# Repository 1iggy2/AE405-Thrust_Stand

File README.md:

# AE405 Thrust Stand

Aero 405 Thrust Stand Project

*By Cameron Gable (1iggy2), Anthony Russo, Hogan Hsu, Sergio Ramirez Sabogal, Brian Sandor*

This project is aimed towards providing a thrust testing stand for brushless electric motors
and propellers used by student project teams as part of Professor George Halow’s AERO 495
course. Prof. Halow has indicated that there is currently a need for some of the project teams that
are part of his course to have an easy way to test the thrust capabilities of their electric motors and
propellers for applications ranging from quadcopters to fixed wing aircraft. Our project concept is
therefore a proposal to design, build, and test a modular thrust test stand that allows for multiple
motor and propeller sizes to be tested safely and effectively by any of the teams participating in
AERO 495. This test stand will use sensors to measure thrust, torque, voltage, current, and RPM
and involve a processing system for automated data collection for simple export to software like
Excel or MatLab for analysis.

Table of Contents
=================

<!--ts-->
   * [Instruction Manual](#instruction-manual)
      * [Safety Considerations](#safety-considerations)
      * [How to Use the Remote](#how-to-use-the-remote)
      * [How to Use the Base Station](#how-to-use-the-base-station)
   * [Construction Guide](#construction-guide)
      * [Wiring](#wiring)
        * [Remote](#remote)
        * [Base Station](#base-station)
      * [Thrust Stand](#thrust-stand)
   * [Design Justification](#design-justification)
      * [Code](#code)
        * [Base Station Logic](base-station-logic)
        * [Remote GUI Explaination](remote-gui-explaination)
      * [Physical Structure Analysis and Testing](physical-structure-analysis-and-testing)
        * [Thrust Stand Simulation](thrust-stand-simulation)
<!--te-->

## Instruction Manual

### Safety Considerations

Be careful when near spinning and/or powered propellers they can and will maim you. Please remove all propellers while working on the thrust stand. Propellers of all sizes are dangerous and deserve your respect. Please use the remote to remain clear of the spinning blades of death, and ensure you have a way to break the physical circuit from a distance.

### How to Use the Remote

The remote connects to the base station using an nRF24L01 radio transciever. When powering on the remote from a computer or USB power supply you will be prompted to select a test to perform. The test selection buttons are on the left hand side of the remote and ordered as seen below:
* TS - Throttle Sweep
* CT - Constant Throttle
* ST - Stress Test

You then will use the ← (left), → (right), and ⌂ (select) buttons to enter your chosen testing parameters. These parameters are:
  
| Parameter |     Description    |  Throttle Sweep |    Constant Throttle    |     Stress Test     |
|:---------:|:------------------:|:---------------:|:-----------------------:|:-------------------:|
|     A     |      Test Type     |        1        |            2            |          3          |
|    BBB    |  Primary Throttle  | Bottom of Sweep | Constant Throttle Value | High Throttle Value |
|    CCC    | Secondary Throttle |   Top of Sweep  |           N/A           |  Low Throttle Value |
|    DDD    |      Test Time     | Total Test Time |     Total Test Time     |   Total Test Time   |
|    EEE    |      Step Time     |    Step Time    |           N/A           |    Switching Time   |

Before clicking to confirm your test selection and start your test you will be presented these values as a final check before sending the data to the base station. This will appear in the form:

* A:BBB:CCC:DDD:EEE

After the data is sent to the base station and the test begins simply click the ⌂ (select) button to send a cancel signal to the base station. In case of communication failure it is always important to have a safe method to physically break the circuit in the case of a catastrophic testing failure. 

### How to Use the Base Station

The base station is a rather hands off piece of equipment. You should not be interacting with it during testing, only monitoring. You may want to set your own safety parameters or recalibrate the test stand. In that case I recommend modifying the parameters in the base station file: [Mega_BaseStation.ino](https://github.com/1iggy2/AE405-Thrust_Stand/blob/main/Mega_BaseStation/Mega_BaseStation.ino) If you do this please submit your calibration to this Github page for posterity. To gather data you will need to insert a FAT32 or FAT16 formatted microSD card into the [Adafruit MicroSD card breakout board+](https://www.adafruit.com/product/254) for the data to be recorded. The data will be recorded to the microSD card in the format shown below. 

| AERO 405 Thrust Stand |                       Winter 2021                      |         |             | Cameron Gable |
|:---------------------:|:------------------------------------------------------:|:-------:|:-----------:|:-------------:|
| Find Documentation at:| [Github](https://github.com/1iggy2/AE405-Thrust_Stand) |         |             |               |
|                       |                                                        |         |             |               |
|  Ambient Conditions:  |                                                        |         |             |               |
|      Temperature:     |                          VALUE                         | Celsius |             |               |
|       Pressure:       |                          VALUE                         | Pascals |             |               |
|                       |                                                        |         |             |               |
|       Thrust(N)       |                          Volts                         |   Amps  | Torque(n-m) |      RPM      |
|         VALUE         |                          VALUE                         |  VALUE  |    VALUE    |     VALUE     |

At this time analysis software is not being developed. It is an important feature to this project, and the relevant issue can be found [here.](https://github.com/1iggy2/AE405-Thrust_Stand/issues/9)

## Construction Guide

### Wiring

#### Remote
The wiring diagram for the remote has been completed in EAGLE. Completed PCB design Gerber files can be found [here.](https://github.com/1iggy2/AE405-Thrust_Stand/tree/main/CAD/RemotePCB) The connections on the diagram below are accurate for anyone who prefers to manufacture it on perf board. (Assembling via a PCB is certainly easier though).

#### Base Station
The wiring diagram for the base station was also completed in EAGLE. However, a PCB has not yet been designed and remains an [issue](https://github.com/1iggy2/AE405-Thrust_Stand/issues/3) for future work.

Please note in the EAGLE image above the pin locations are not accurate on the Arduino Mega, instead the nets have been named [PIN-PURPOSE].

### Thrust Stand

Our thrust stand has been designed with modularity as the main objective. The interchangeable
vertical arm lengths allow for testing to occur for a variety of propeller and motor sizes. This also
allows for the thrust stand to operate in both large and small wind tunnels, making test scheduling more convenient for the users. Our motor mounting plates will allow for the mounting of
various motors with different bolt patterns. The various sizes of these plates will allow for testing
on small motors and large motors on the same stand. 

Long Arm Render             |  Short Arm Render
  :-------------------------:|:-------------------------:
  |  

Our unique flexure torque measurement
device, seen below, allows for torque data to be collected from all ranges of motor sizes that fit on the thrust
testing stand. This innovation increases the effectiveness and accuracy of the data from other more
traditional torque measurement solutions. These system design choices increase the effectiveness
of our thrust stand and allow it to meet a wide variety of team’s thrust testing needs.

Our design also features a pivot comprised of two pillow blocks to minimize any stiction, or static friction. A beautiful render of this pivot is shown below. A majority of the parts purchased for the structural construction came from McMaster Carr.

## Design Justification

### Code

#### Base Station Logic

The Base Station is the measurement and data acquistion hub of this project. Tests will be run based on the Menu ID sent from the remote. Raw sensor output, calibration, and settings will be accessed via a physical button press and the serial monitor. This is due to RAM limitations in the Arduino Nano powering the Remote. A full flowchart of the logic is provided below.

#### Remote GUI Explaination

After initial testing of the remote GUI intiailly proposed it was apparent that the Arduino Nano did not have enough RAM to display the fully fleshed out GUI. In order to combat this we have designed a low menu count GUI to optimize the remote. This menu uses a minimal amount of unique screens to lower the RAM usage. The image below is the design flowchart for the optimized remote.

### Physical Structure Analysis

#### Thrust Stand Simulation

In order to model the thrust stand system in FEA many of the complex structures
were simplified. This included the flexure assembly being modelled as a rectangular block and
the bearing pivot being modelled as a bearing fixture. The CAD model was done in Solidworks
and the FEA was done in the Solidworks built-in simulation tool. The load cell and the sides of the
pivot were modelled as roller/slider fixtures so that they would be constrained in the plane but
can move laterally. The built-in 6061 aluminum alloy material model was applied to the model
due to convenience, which has the same properties as the 6105-T5 alloy, just a lower yield strength.
The mesh was generated using Solidworks’ automated mesh tool, but mesh control was applied
in order to ensure that there were at least 3 elements across each dimension to accurately model
the problem. In the image below, a zoomed in display of the maximum stress point is shown along with
the mesh for the max loading condition of 20 lbf of thrust and 15 lbf-in of torque on the long
arm model. The maximum stress ended up being in the same region for all the simulations, right
where the 90◦ bracket met the horizontal arm.

Another accuracy concern is the drag produced by inlet air during wind tunnel testing, particularly
on the vertical arm of the test stand. The load cell measuring thrust will not be able to distinguish between this drag force and a thrust difference, thus reducing accuracy. To make sure that
our measurement is as accurate as possible during these testing circumstances, we surveyed various cross-sectional shapes of the vertical beam using CFD simulations. STAR-CCM+ CFD simulations were used to model the drag of the
stand. Because the only variable between these design is the vertical beam cross-section, simulations were performed using the 15 inch beam by itself, with semicircular fairings, and with one
semicircular fairing on the front face and an elliptical section on the rear face to give the overall cross-section an airfoil shape. Seen in the table below.

| No Fairing | Semi-Circular Fairing | Airfoil Fairing |
|------------|-----------------------|-----------------|
|       |                  |            |

The simulations were then run with the respective beam suspended,
centered in a simulated 2 foot X 2 foot wind tunnel using iterations with intake airspeed of 11, 22,
34, 45, 56, and 67 miles per hour. The results are shown in the table below.

Plotted into a graph:

With this information we are designing a 3D printed airfoil to slot into the 8020 aluminium extrusion. We will also be putting our structure, shrouded with an aerodynamic
fairing, into the wind tunnel and testing the amount of drag that the system generates with the
goal of minimizing this effect. This will be to validate our simulations. 

We chose to use a NACA 0015 airfoil fairing for the vertical arm of the stand.

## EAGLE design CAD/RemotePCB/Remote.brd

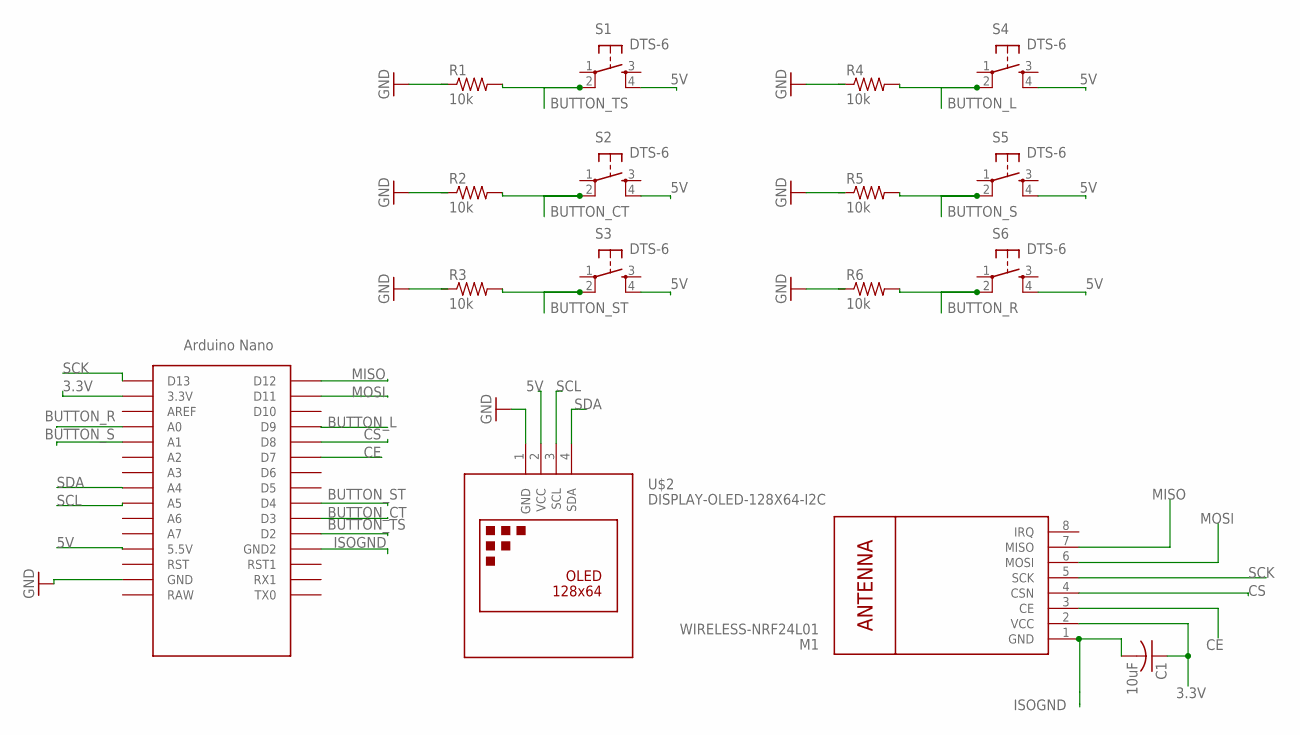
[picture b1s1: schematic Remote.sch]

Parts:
C1: 10uF; C025-030X050
M1: WIRELESS-NRF24L01
R1, R2, R3, R4, R5, R6: 10k; 0207/10
S1, S2, S3, S4, S5, S6: DTS-6
U$1: NANO
U$2: DISPLAY-OLED-128X64-I2C

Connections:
3.3V: C1.1, M1.2 (VCC), U$1.3.3V
5V: S1.4, S2.4, S3.4, S4.4, S5.4, S6.4, U$1.5V (5.5V), U$2.2 (VCC)
BUTTON_CT: R2.2, S2.2, U$1.D3
BUTTON_L: R4.2, S4.2, U$1.D9
BUTTON_R: R6.2, S6.2, U$1.A0
BUTTON_S: R5.2, S5.2, U$1.A1
BUTTON_ST: R3.2, S3.2, U$1.D4
BUTTON_TS: R1.2, S1.2, U$1.D2
CE: M1.3 (CE), U$1.D7
CS: M1.4 (CSN), U$1.D8
GND: R1.1, R2.1, R3.1, R4.1, R5.1, R6.1, U$1.GND, U$2.1 (GND)
ISOGND: C1.2, M1.1 (GND), U$1.GND1 (GND2)
MISO: M1.7 (MISO), U$1.D12
MOSI: M1.6 (MOSI), U$1.D11
SCK: M1.5 (SCK), U$1.D13
SCL: U$1.A5, U$2.3 (SCL)
SDA: U$1.A4, U$2.4 (SDA)

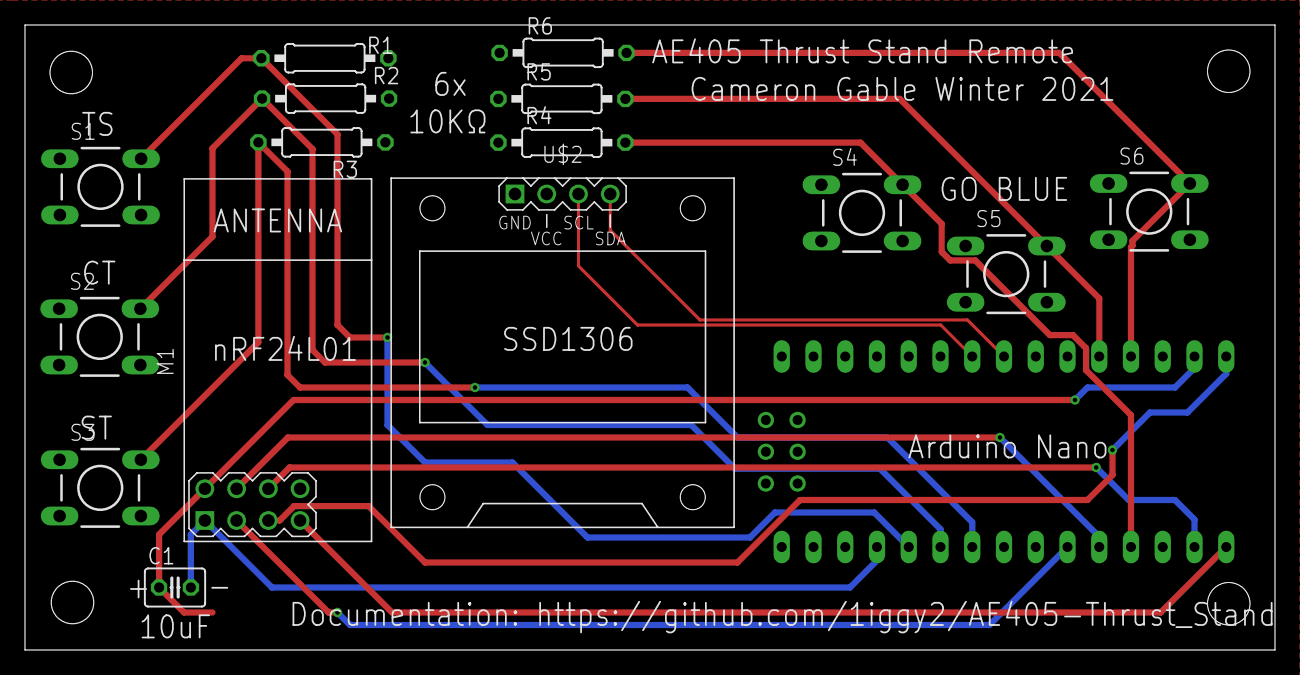
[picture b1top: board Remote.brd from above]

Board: 2 copper layers, 100.0 x 50.0 mm, 16 parts (0 on the bottom side), 17 nets.

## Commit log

2021-02-21 Initial Commit, adding previous Arduino Code
2021-02-21 White Paper
2021-02-21 Add placeholder base station file
2021-02-21 Placeholder RPPico Remote Screen File
2021-02-22 Add Umich Aero Banner to Readme
2021-02-28 Updated folder structure for development
2021-03-16 Base Station Outlined
2021-03-16 Base Station Outlined & New Libraries Added
2021-03-16 Established new GUI
2021-03-16 Minor Tweaks
2021-03-16 Updated flowcharts to reflect Sensor Output, Calibration, and Settings buttons on Base Station
2021-03-16 Centered flowchart in readme
2021-03-16 Started Base Station Logic Flowchart
2021-03-16 Modeled Base Station Logic
2021-03-16 Added Base Station Logic section to README
2021-03-17 Remote w/ Buttons code laid out, not hardware tested
2021-03-17 Add images, Phase 1 Report, Update Remote w/ Buttons
2021-03-17 Spruce up Readme with physical information.
2021-03-17 added drag table
2021-03-17 Additional information added to the README
2021-03-17 Breakthrough on SSD1306 RAM, BEAUTIFUL LIBRARY
2021-03-17 Add More Images
2021-03-17 rotated AerofairingXsect
2021-03-17 add circuito.io images
2021-03-17 Add circuito remote diagrams to readme
2021-03-18 Add base station images
2021-03-18 Updated readme structure, base station wiring guide
2021-03-18 Added Table of Contents
2021-03-19 Remote working, RF not tested
2021-03-19 Added Soldiworks models and Manufactured drawings
2021-03-20 nRF24L01 Test Failed
2021-03-20 Modified Address Check
2021-03-24 Some communication. Not reliable
2021-03-27 Reliable communication established
2021-03-28 Added Radio and Timing to Base
    Implemented the radio code from BaseStationRadioTest into the main base station function. Tested and working. Implemented millis() based timing to the three test types. Tested and functional. Establi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
2021-03-31 Wrote calibration sketch
    For wiring see comments on the top of the arduino sketch
2021-04-09 Wrote Hall data test into calibration sketch
2021-04-09 Cleaned up repo a little
2021-04-09 Further cleaning
2021-04-11 Remote Case CAD upload
2021-04-11 PCB Designed
2021-04-11 added Screenshots
2021-04-14 Added BME280 to code. Tested and working
2021-04-14 Added SD Card support, not tested
    Woot woot
2021-04-17 Calibration sketch integrated into Base Station Main
    Integrated the tested calibration sketch into the main base station code for testing this weekend. Also uploaded rough EAGLE diagram for base station and removed unnecesarry library. Future Work: Imp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
2021-04-18 Troubleshootiung
2021-04-18 Troubleshootiung V2
2021-04-18 Troubleshooting V3
2021-04-18 Troubleshooting V4 Removed SD
2021-04-18 Troubleshooting V6 ReAdded SD
2021-04-19 Found ESC.attach or ESC.writeMicroseconds breaks everything... Will fix
2021-04-19 Was a redeclaration of the CE_PIN for the nRF24L01... Corrected
2021-04-20 Token Test
2021-04-20 Token Test 2
2021-04-20 RPM collection added. Not tested
2021-04-20 Intermediate update
2021-04-20 Adding more images and Poster
2021-04-20 Add Case Image
2021-04-20 Turn README into a Manual
    Need to add a BoM including part links, rework the justification section as necessary, and generally polish up the README.
2021-04-20 Tweaked SD Card data output
    Reworked header and included the RPM measurements
2021-04-21 Uncomment ESC code
2021-04-21 Debugging Serail Prints
2021-04-21 Debugging Serial Prints V2
2021-04-21 Debugging 3
2021-04-21 Debugging 4
2021-04-21 Debugging 5
2021-04-21 Debugging 6
2021-04-21 Debugging 7
2021-04-21 Debugging 8
2021-04-21 LC, Torque, and Voltage Calibrated
2021-04-21 Removed GCode
2021-04-21 SD Debug 1
2021-04-21 SD Debug 2, working
2021-04-21 SD Output Tweaks
    Added time, redid voltage calibration, recentered torque sensor
2021-04-21 Iterative file creation
2021-04-21 Added remote PCB assembled image
2021-04-21 Throttle added, file iteration worked on
2021-04-22 Current Calibration and SD file it change
2021-04-22 SD header revamped
2021-04-22 Add data import image
2021-04-22 Changed some ints to floats
2021-04-22 Cast ints to floats
2021-04-22 Current Calibration update
2021-04-22 Minor header tweak
2021-04-24 Final Report Completed

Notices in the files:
parts and their libraries:
diy-modules: Released under the Creative Commons Attribution 4.0 International License: http://creativecommons.org/licenses/by/4.0
